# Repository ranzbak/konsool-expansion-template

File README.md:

# Expansion template

## Introduction

Basic empty Konsool expansion, with te correct dimensions between the connector and the mounting holes.

## Orientation

The board oriention is seen from the front of the Konsool.
- Front on the PCB will point inwards, hence towards the konsool.
- Back of the PCB will be pointing outwards

Any high components or components that need user interaction need to be placed an the back side of the PCB.

# Outline

That the outline is kept smaller than the outline of the Konsool PCB, this is done so there is
room for the housing to wrap around the board. 
The board edge can be modified as needed, given a custom housing needs to be designed in most cases.

# Features

- Connector

# Requirements

- Imagination

## License

Copyright Ranzbak [Badge.Team](https://badge.team) 2025

[This source describes Open Hardware and is licensed under the CERN-OHL-P v2](https://cern-ohl.web.cern.ch/home)

You may redistribute and modify this documentation and make products
using it under the terms of the CERN-OHL-P v2 (https:/cern.ch/cern-ohl).
This documentation is distributed WITHOUT ANY EXPRESS OR IMPLIED
WARRANTY, INCLUDING OF MERCHANTABILITY, SATISFACTORY QUALITY
AND FITNESS FOR A PARTICULAR PURPOSE. Please see the CERN-OHL-P v2
for applicable conditions

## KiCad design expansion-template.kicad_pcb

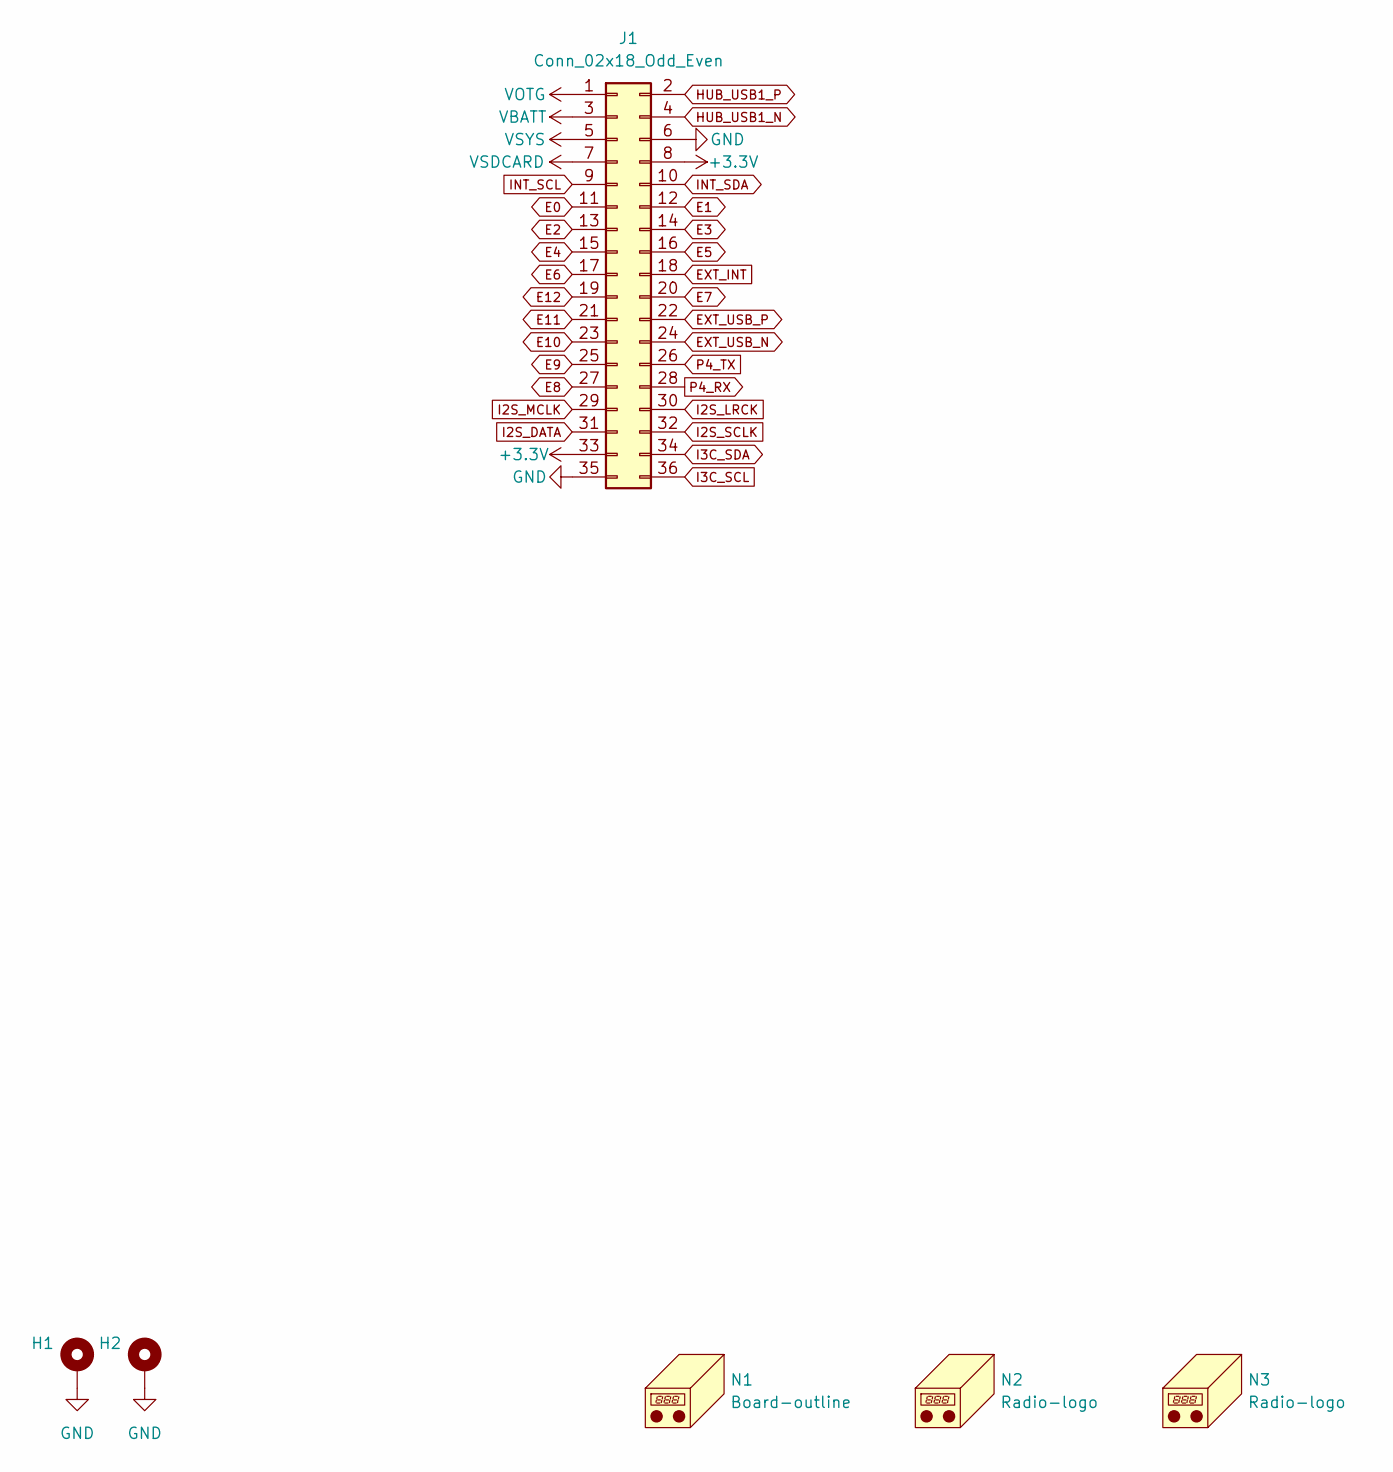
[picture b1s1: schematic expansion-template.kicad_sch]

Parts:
H1, H2: Mounting hole; MountingHole_2.2mm_M2_DIN965_Pad
J1: Conn_02x18_Odd_Even; PinHeader_2x18_P2.54mm_Vertical; LCSC C3294476
N1: Board-outline; why2025-mainboard-edge-cuts-usr
N2, N3: Radio-logo; radio_logo

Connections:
+3.3V: J1.8, J1.33
E0: J1.11
E1: J1.12
E2: J1.13
E3: J1.14
E4: J1.15
E5: J1.16
E6: J1.17
E7: J1.20
E8: J1.27
E9: J1.25
E10: J1.23
E11: J1.21
E12: J1.19
EXT_INT: J1.18
EXT_USB_N: J1.24
EXT_USB_P: J1.22
GND: H1.1, H2.1, J1.6, J1.35
HUB_USB1_N: J1.4
HUB_USB1_P: J1.2
I2S_DATA: J1.31
I2S_LRCK: J1.30
I2S_MCLK: J1.29
I2S_SCLK: J1.32
I3C_SCL: J1.36
I3C_SDA: J1.34
INT_SCL: J1.9
INT_SDA: J1.10
P4_RX: J1.28
P4_TX: J1.26
VBATT: J1.3
VOTG: J1.1
VSDCARD: J1.7
VSYS: J1.5

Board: 4 copper layers, 44 parts (2 on the bottom side), 2 nets, no tracks yet.

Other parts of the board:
kibuzzard-672DEDFD: G***; kibuzzard-672DEDFD
kibuzzard-672DEE22: G***; kibuzzard-672DEE22
kibuzzard-672F44AA: G***; kibuzzard-672F44AA
kibuzzard-672F44B3: G***; kibuzzard-672F44B3
kibuzzard-672F44C7: G***; kibuzzard-672F44C7
kibuzzard-672F44D7: G***; kibuzzard-672F44D7
kibuzzard-672F44E2: G***; kibuzzard-672F44E2
kibuzzard-672F44E9: G***; kibuzzard-672F44E9
kibuzzard-672F44F4: G***; kibuzzard-672F44F4
kibuzzard-672F44FC: G***; kibuzzard-672F44FC
kibuzzard-672F45AF: G***; kibuzzard-672F45AF
kibuzzard-672F45BC: G***; kibuzzard-672F45BC
kibuzzard-672F45CE: G***; kibuzzard-672F45CE
kibuzzard-672F45D8: G***; kibuzzard-672F45D8
kibuzzard-672F45E8: G***; kibuzzard-672F45E8
kibuzzard-672F45EE: G***; kibuzzard-672F45EE
kibuzzard-672F45F5: G***; kibuzzard-672F45F5
kibuzzard-672F417C: G***; kibuzzard-672F417C
kibuzzard-672F452F: G***; kibuzzard-672F452F
kibuzzard-672F459A: G***; kibuzzard-672F459A
kibuzzard-672F460D: G***; kibuzzard-672F460D
kibuzzard-672F461C: G***; kibuzzard-672F461C
kibuzzard-672F463A: G***; kibuzzard-672F463A
kibuzzard-672F465A: G***; kibuzzard-672F465A
kibuzzard-672F466D: G***; kibuzzard-672F466D
kibuzzard-672F467D: G***; kibuzzard-672F467D
kibuzzard-672F4509: G***; kibuzzard-672F4509
kibuzzard-672F4510: G***; kibuzzard-672F4510
kibuzzard-672F4516: G***; kibuzzard-672F4516
kibuzzard-672F4522: G***; kibuzzard-672F4522
kibuzzard-672F4544: G***; kibuzzard-672F4544
kibuzzard-672F4557: G***; kibuzzard-672F4557
kibuzzard-672F4561: G***; kibuzzard-672F4561
kibuzzard-672F4600: G***; kibuzzard-672F4600
kibuzzard-672F4627: G***; kibuzzard-672F4627
kibuzzard-672F4631: G***; kibuzzard-672F4631
kibuzzard-672F4648: G***; kibuzzard-672F4648
kibuzzard-672F4776: G***; kibuzzard-672F4776

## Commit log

2025-03-23 First checkin.
2025-03-23 Add basic description for template application.
